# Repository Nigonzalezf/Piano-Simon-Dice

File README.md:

# Simon's Piano 
Proyecto taller de ingeniería electrónica unal 2024-1

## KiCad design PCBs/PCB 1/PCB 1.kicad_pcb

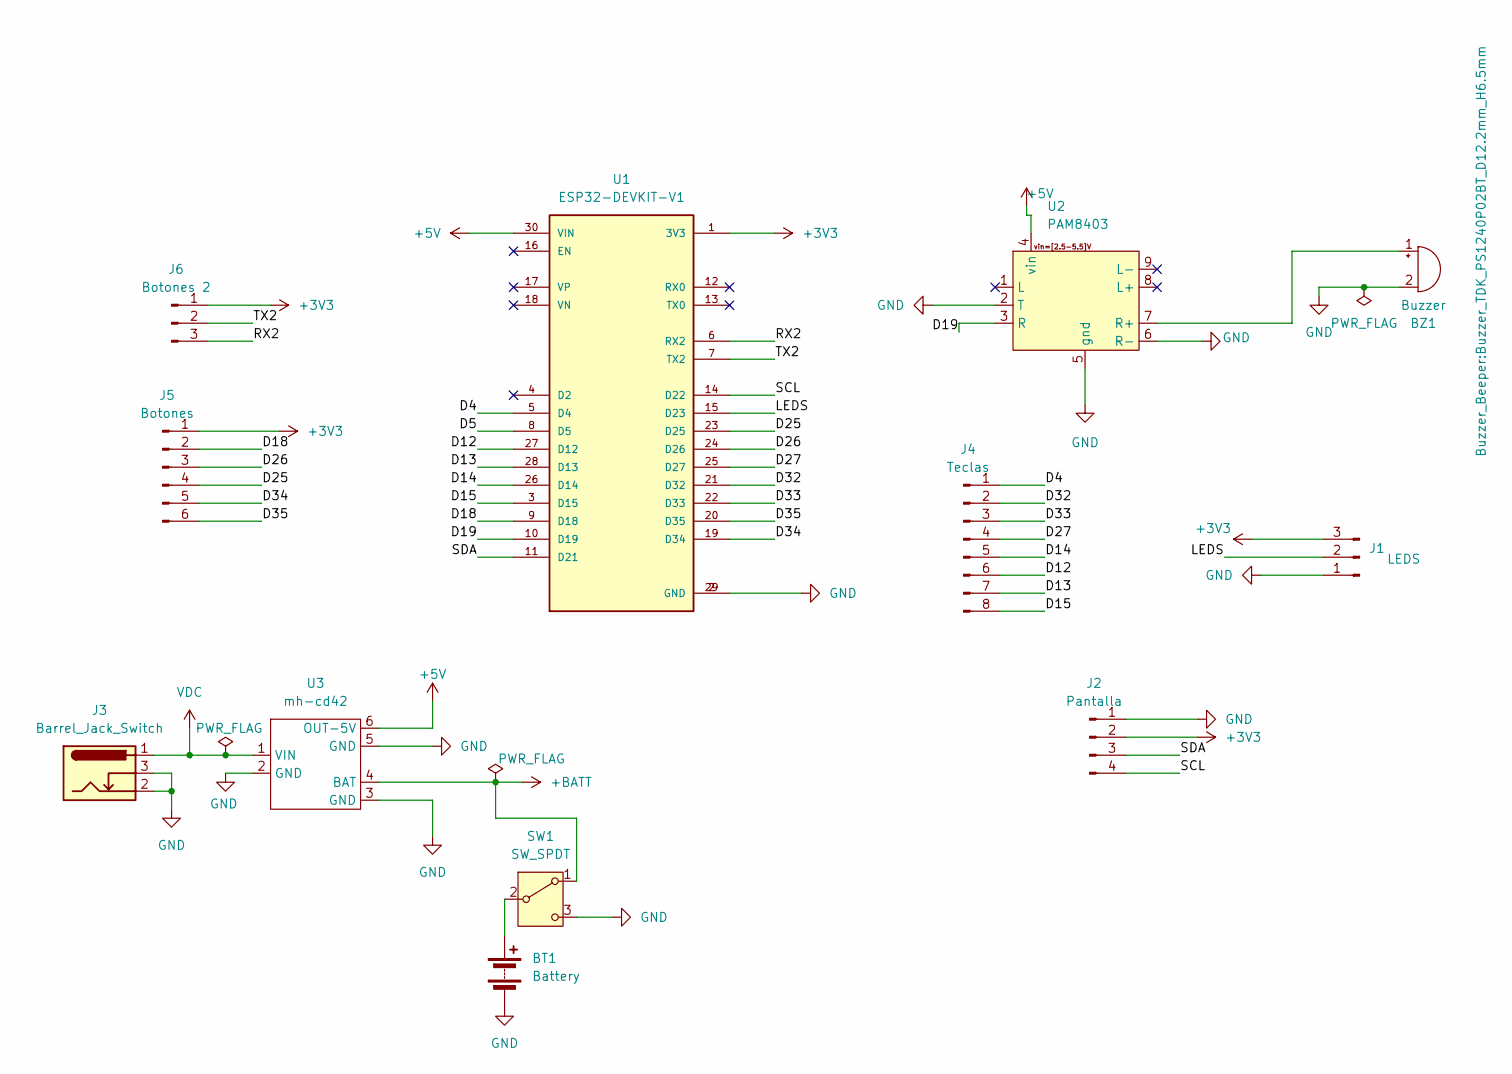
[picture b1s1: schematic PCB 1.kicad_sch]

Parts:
BT1: Battery; BatteryHolder_MPD_BH-18650-PC2
BZ1: Buzzer; Buzzer_TDK_PS1240P02BT_D12.2mm_H6.5mm
J1: LEDS; FanPinHeader_1x03_P2.54mm_Vertical
J2: Pantalla; PinSocket_1x04_P2.54mm_Vertical
J3: Barrel_Jack_Switch; BarrelJack_Horizontal
J4: Teclas; PinSocket_1x08_P2.54mm_Vertical
J5: Botones; PinSocket_1x06_P2.54mm_Vertical
J6: Botones 2; PinSocket_1x03_P2.54mm_Vertical
SW1: SW_SPDT; SW_DIP_SPSTx02_Slide_6.7x6.64mm_W7.62mm_P2.54mm_LowProfile
U1: ESP32-DEVKIT-V1; MODULE_ESP32_DEVKIT_V1; PARTREV N/A
U2: PAM8403; pam8403
U3: mh-cd42

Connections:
+3V3: J1.3, J2.2, J5.1, J6.1, U1.1 (3V3)
+5V: U1.30 (VIN), U2.4 (vin), U3.6 (OUT-5V)
+BATT: SW1.1 (A), U3.4 (BAT)
/D4: J4.1, U1.5 (D4)
/D5: U1.8 (D5)
/D12: J4.6, U1.27 (D12)
/D13: J4.7, U1.28 (D13)
/D14: J4.5, U1.26 (D14)
/D15: J4.8, U1.3 (D15)
/D18: J5.2, U1.9 (D18)
/D19: U1.10 (D19), U2.3 (R)
/D25: J5.4, U1.23 (D25)
/D26: J5.3, U1.24 (D26)
/D27: J4.4, U1.25 (D27)
/D32: J4.2, U1.21 (D32)
/D33: J4.3, U1.22 (D33)
/D34: J5.5, U1.19 (D34)
/D35: J5.6, U1.20 (D35)
/LEDS: J1.2, U1.15 (D23)
/RX2: J6.3, U1.6 (RX2)
/SCL: J2.4, U1.14 (D22)
/SDA: J2.3, U1.11 (D21)
/TX2: J6.2, U1.7 (TX2)
GND: BT1.2 (-), BZ1.2 (-), J1.1, J2.1, J3.2, J3.3, SW1.3 (C), U1.2 (GND), U1.29 (GND), U2.2 (T), U2.5 (gnd), U2.6 (R-), U3.2 (GND), U3.3 (GND), U3.5 (GND)
unnamed: BT1.1 (+), SW1.2 (B)
unnamed: BZ1.1 (+), U2.7 (R+)
VDC: J3.1, U3.1 (VIN)

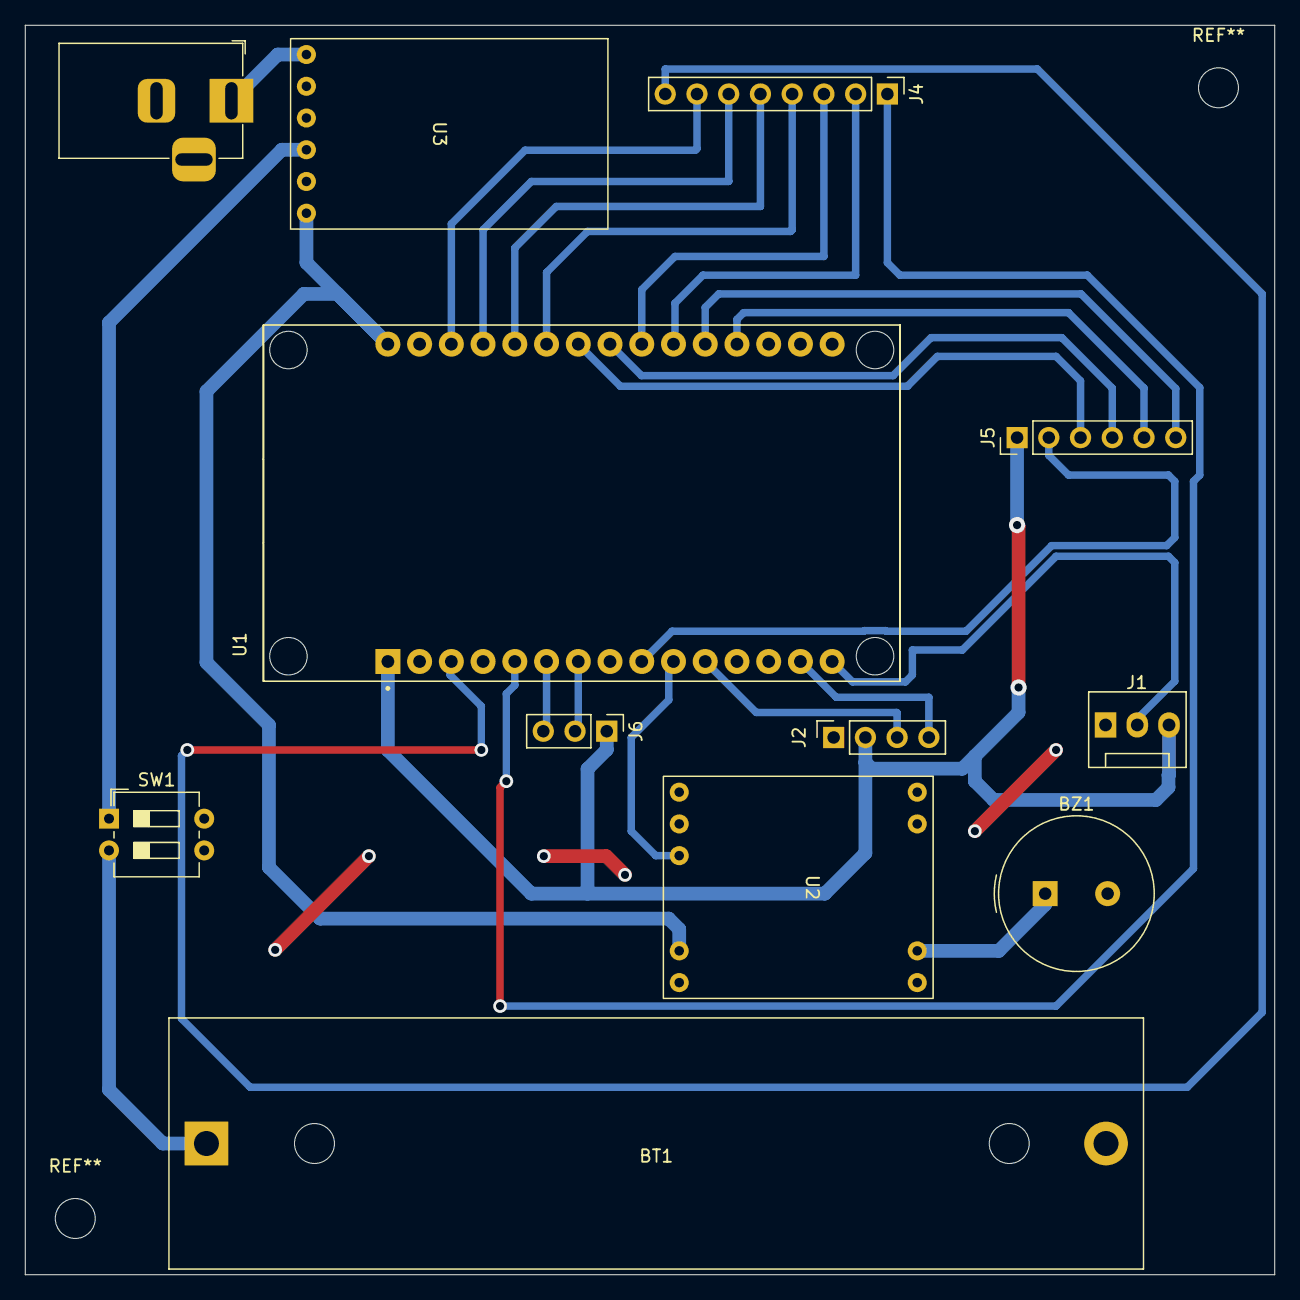
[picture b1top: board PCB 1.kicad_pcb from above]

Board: 2 copper layers, 100.0 x 100.0 mm, 12 parts (0 on the bottom side), 26 nets.

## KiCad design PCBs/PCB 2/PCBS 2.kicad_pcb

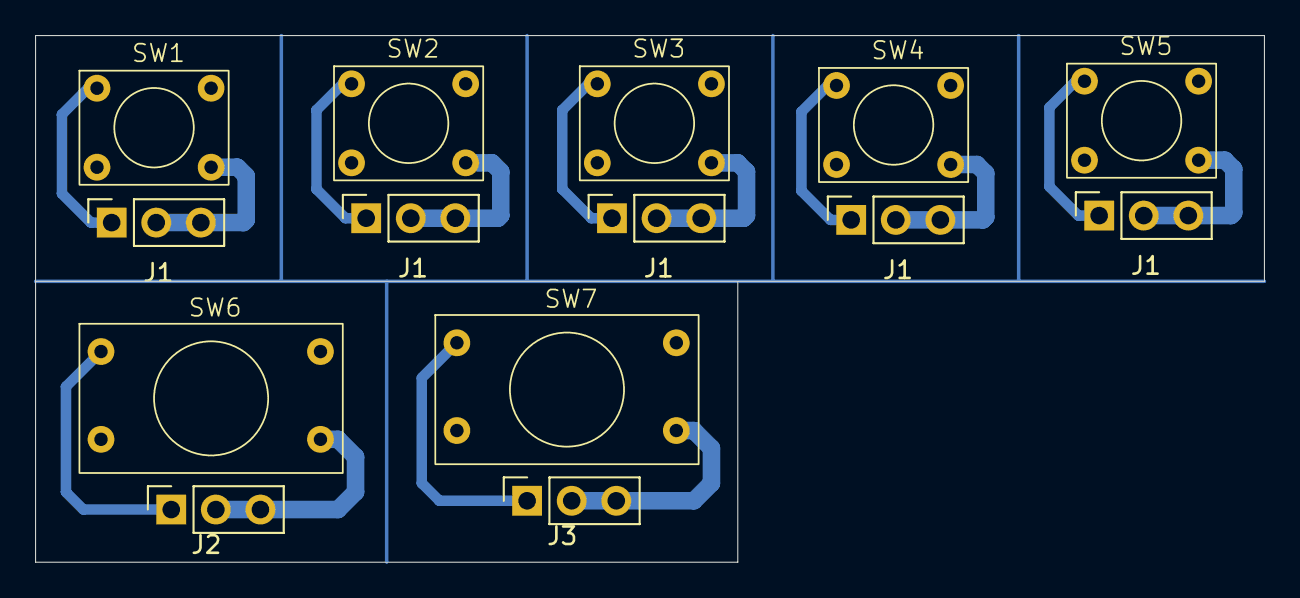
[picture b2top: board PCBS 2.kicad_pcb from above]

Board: 2 copper layers, 70.0 x 30.0 mm, 14 parts (0 on the bottom side), 2 nets.

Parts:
J1, J1#2, J1#3, J1#4, J1#5, J2, J3: Conn_01x03_Pin; PinSocket_1x03_P2.54mm_Vertical
SW1, SW2, SW3, SW4, SW5: SW_DIP_x02; Micro Pulsador
SW6, SW7: SW_DIP_x02; Pulsador grande

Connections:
/D1: J1.1, J1#2.1, J1#3.1, J1#4.1, J1#5.1, J2.1, J3.1, SW1.1, SW2.1, SW3.1, SW4.1, SW5.1, SW6.1, SW7.1
GND: J1.2, J1.3, J1#2.2, J1#2.3, J1#3.2, J1#3.3, J1#4.2, J1#4.3, J1#5.2, J1#5.3, J2.2, J2.3, J3.2, J3.3, SW1.4, SW2.4, SW3.4, SW4.4, SW5.4, SW6.4, SW7.4

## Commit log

2024-08-27 Spelling correction
    Ingeniris -> Ingeniería
2024-09-10 .gitignore
2024-09-10 Se añade la documentación PROFI
2024-09-10 Se añade nuevamente la documentación PROFI
2024-09-15 Archivos PCBs
2024-09-15 Visualizaciones PCB
2024-09-25 STL Piano
2024-09-25 Añadir archivos PCB
2024-09-25 Imagenes añadidas
2024-09-25 Se añaden png de esquema y ruteo
2024-09-25 Se añaden PCB
2024-09-26 se añade .py wokwi
